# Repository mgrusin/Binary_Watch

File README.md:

Binary_Watch
============

A binary watch for fun

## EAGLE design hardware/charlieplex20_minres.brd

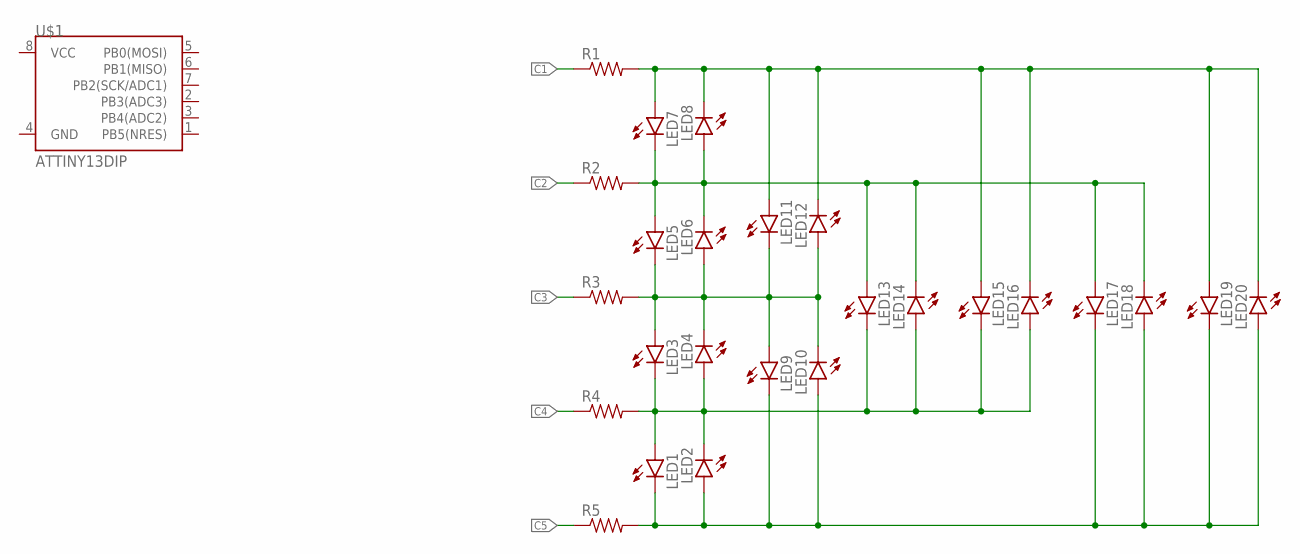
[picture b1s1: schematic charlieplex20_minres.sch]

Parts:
LED1, LED2, LED3, LED4, LED5, LED6, LED7, LED8, LED9, LED10, LED11, LED12, LED13, LED14, LED15, LED16, LED17, LED18, LED19, LED20: LED0603; LED-0603
R1, R2, R3, R4, R5: RESISTOR0603-RES; 0603-RES
U$1: ATTINY13DIP; DIP08

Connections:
C1: LED7.A, LED8.C, LED11.A, LED12.C, LED15.A, LED16.C, LED19.A, LED20.C, R1.1, R1.2
C2: LED5.A, LED6.C, LED7.C, LED8.A, LED13.A, LED14.C, LED17.A, LED18.C, R2.1, R2.2
C3: LED3.A, LED4.C, LED5.C, LED6.A, LED9.A, LED10.C, LED11.C, LED12.A, R3.1, R3.2
C4: LED1.A, LED2.C, LED3.C, LED4.A, LED13.C, LED14.A, LED15.C, LED16.A, R4.1, R4.2
C5: LED1.C, LED2.A, LED9.C, LED10.A, LED17.C, LED18.A, LED19.C, LED20.A, R5.1, R5.2

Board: 2 copper layers, 26 parts (0 on the bottom side), 5 nets, no tracks yet.

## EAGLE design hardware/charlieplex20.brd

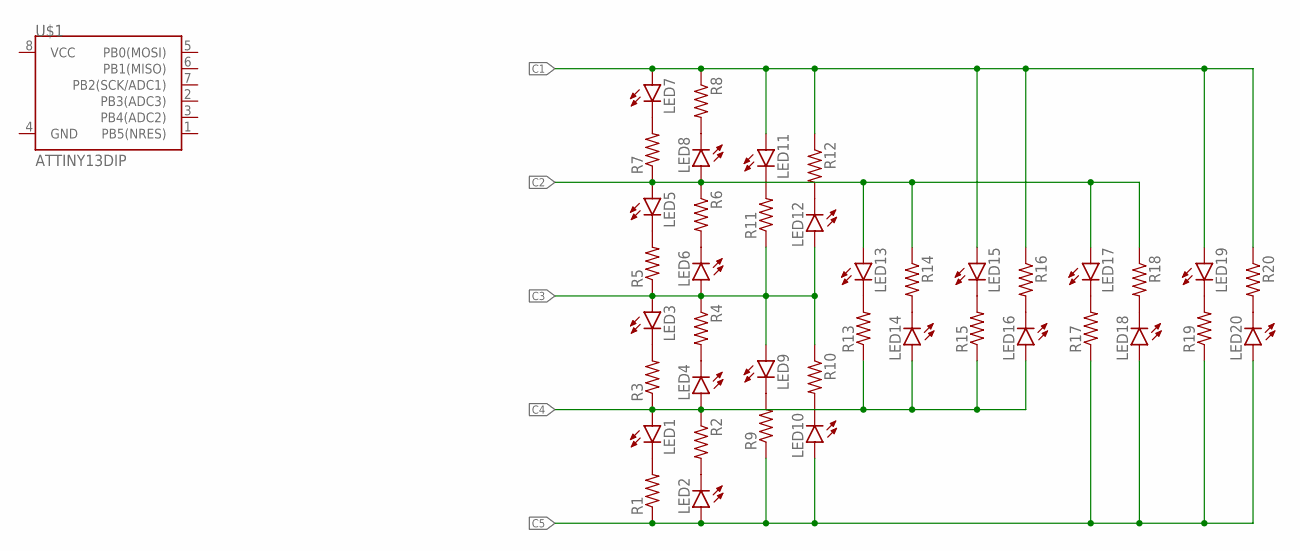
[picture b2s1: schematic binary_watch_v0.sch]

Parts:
LED1, LED2, LED3, LED4, LED5, LED6, LED7, LED8, LED9, LED10, LED11, LED12, LED13, LED14, LED15, LED16, LED17, LED18, LED19, LED20: LED0603; LED-0603
R1, R2, R3, R4, R5, R6, R7, R8, R9, R10, R11, R12, R13, R14, R15, R16, R17, R18, R19, R20: RESISTOR0603-RES; 0603-RES
U$1: ATTINY13DIP; DIP08

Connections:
C1: LED7.A, LED11.A, LED15.A, LED19.A, R8.1, R12.1, R16.1, R20.1
C2: LED5.A, LED8.A, LED13.A, LED17.A, R6.1, R7.1, R14.1, R18.1
C3: LED3.A, LED6.A, LED9.A, LED12.A, R4.1, R5.1, R10.1, R11.1
C4: LED1.A, LED4.A, LED14.A, LED16.A, R2.1, R3.1, R13.1, R15.1
C5: LED2.A, LED10.A, LED18.A, LED20.A, R1.1, R9.1, R17.1, R19.1
unnamed: LED1.C, R1.2
unnamed: LED2.C, R2.2
unnamed: LED3.C, R3.2
unnamed: LED4.C, R4.2
unnamed: LED5.C, R5.2
unnamed: LED6.C, R6.2
unnamed: LED8.C, R8.2
unnamed: LED7.C, R7.2
unnamed: LED9.C, R9.2
unnamed: LED10.C, R10.2
unnamed: LED11.C, R11.2
unnamed: LED12.C, R12.2
unnamed: LED13.C, R13.2
unnamed: LED14.C, R14.2
unnamed: LED15.C, R15.2
unnamed: LED16.C, R16.2
unnamed: LED17.C, R17.2
unnamed: LED18.C, R18.2
unnamed: LED19.C, R19.2
unnamed: LED20.C, R20.2

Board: 2 copper layers, 41 parts (0 on the bottom side), 25 nets, no tracks yet.

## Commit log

2014-09-16 Initial (real) commit

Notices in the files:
parts and their libraries:
SparkFun-LED: Licensing: Creative Commons ShareAlike 4.0 International - https://creativecommons.org/licenses/by-sa/4.0
